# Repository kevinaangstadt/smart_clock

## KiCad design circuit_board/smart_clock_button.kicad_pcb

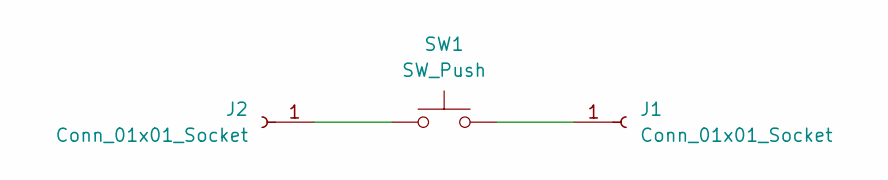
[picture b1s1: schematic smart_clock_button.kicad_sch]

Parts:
J1, J2: Conn_01x01_Socket; TestPoint_THTPad_1.5x1.5mm_Drill0.7mm
SW1: SW_Push; SW_PUSH_6mm_H9.5mm

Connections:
unnamed: J1.1, SW1.2
unnamed: J2.1, SW1.1

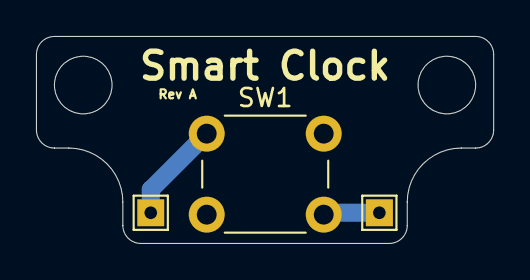
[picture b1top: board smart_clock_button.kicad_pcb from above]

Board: 2 copper layers, 25.4 x 11.5 mm, 3 parts (0 on the bottom side), 2 nets.

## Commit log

2025-09-06 First version of full software
2025-09-06 PCB for button
2025-09-06 Updated circuit board
2026-01-02 fix DST handling
2026-01-02 Improved ntp handling
2026-01-04 attempting time calibration improvements
2026-05-10 Update timezone api to cloudflare worker
